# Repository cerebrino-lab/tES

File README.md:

# diy_tES
Eletro-estimulador transcraniano (tES)

## ATENÇÃO!
**Esse circuito pode causar danos graves e permanentes ou até a morte.
O projeto foi publicado apenas para fiz didátidos e não deve ser usado em seres humanos ou animais em hipótese alguma.
Estejam cientes!**

## Configuração dos parâmetros através de conexão serial.

Modos de operação:
-Modo corrente contínua (ainda não implementado): estímulo por corrente contínua ajustavel de 0mA á 2mA 
-Modo senoidal: onda senoidal simples, com frequência ajustavel de 1Hz á 255Hz e corrente de 0mA á 2mA pico a pico.
-Modo cruzado: onda senoidal modulada em amplitude na fase positiva por uma segunda onda. Frequências com ajuste independente de 1Hz á 255Hz e correntes de 0mA á 2mA pico a pico.
Parâmetros das ondas:

-Frequência: ajustável de 1 a 255 Hz.

-Amplitude: ajustável de 0.1 a 2,1mA.

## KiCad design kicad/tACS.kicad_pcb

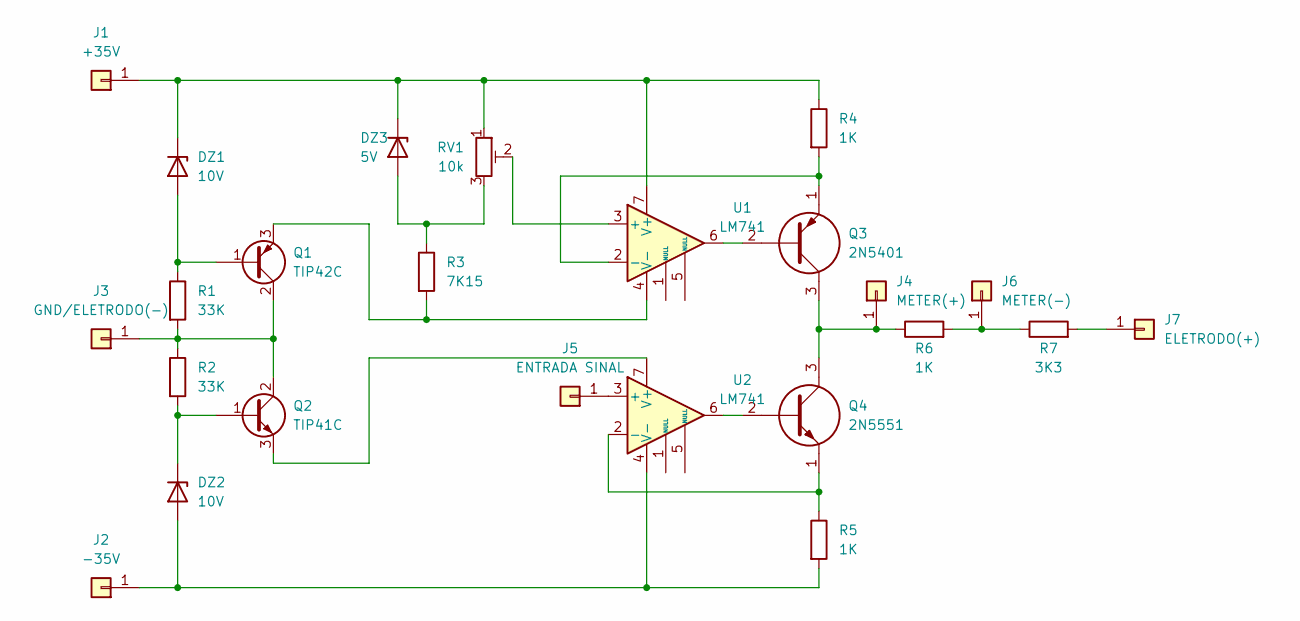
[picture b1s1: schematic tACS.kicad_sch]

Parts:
DZ1, DZ2: 10V; D_DO-41_SOD81_P7.62mm_Horizontal
DZ3: 5V; D_DO-41_SOD81_P7.62mm_Horizontal
J1: +35V; Pin_D0.7mm_L6.5mm_W1.8mm_FlatFork
J2: -35V; Pin_D0.7mm_L6.5mm_W1.8mm_FlatFork
J3: GND/ELETRODO(-); Pin_D0.7mm_L6.5mm_W1.8mm_FlatFork
J4: METER(+); Pin_D0.7mm_L6.5mm_W1.8mm_FlatFork
J5: ENTRADA SINAL; Pin_D0.7mm_L6.5mm_W1.8mm_FlatFork
J6: METER(-); Pin_D0.7mm_L6.5mm_W1.8mm_FlatFork
J7: ELETRODO(+); Pin_D0.7mm_L6.5mm_W1.8mm_FlatFork
Q1: TIP42C; TO-220-3_Vertical
Q2: TIP41C; TO-220-3_Vertical
Q3: 2N5401; TO-92; Manufacturer_Part_Number 2N5401
Q4: 2N5551; TO-92; Manufacturer_Part_Number 2N5551; Mouser Part Number 863-2N5551
R1, R2: 33K; R_Axial_DIN0204_L3.6mm_D1.6mm_P7.62mm_Horizontal
R3: 7K15; R_Axial_DIN0204_L3.6mm_D1.6mm_P7.62mm_Horizontal
R4, R6: 1K; R_Axial_DIN0204_L3.6mm_D1.6mm_P7.62mm_Horizontal
R5: 1K; R_Axial_DIN0204_L3.6mm_D1.6mm_P5.08mm_Vertical
R7: 3K3; R_Axial_DIN0204_L3.6mm_D1.6mm_P7.62mm_Horizontal
RV1: 10k; Potentiometer_Bourns_3296W_Vertical
U1, U2: LM741; DIP-8_W7.62mm_LongPads

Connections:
unnamed: DZ1.2 (A), Q1.1 (B), R1.1
unnamed: DZ1.1 (K), DZ3.1 (K), J1.1, R4.1, RV1.1, U1.7 (V+)
unnamed: DZ2.2 (A), J2.1, R5.2, U2.4 (V-)
unnamed: DZ2.1 (K), Q2.1 (B), R2.2
unnamed: DZ3.2 (A), R3.1, RV1.3
unnamed: J3.1, Q1.2 (C), Q2.2 (C), R1.2, R2.1
unnamed: J4.1, Q3.3, Q4.3, R6.1
unnamed: J5.1, U2.3 (+)
unnamed: J6.1, R6.2, R7.1
unnamed: J7.1, R7.2
unnamed: Q1.3 (E), R3.2, U1.4 (V-)
unnamed: Q2.3 (E), U2.7 (V+)
unnamed: Q3.2, U1.6
unnamed: Q4.2, U2.6
unnamed: RV1.2, U1.3 (+)
unnamed: Q3.1, R4.2, U1.2 (-)
unnamed: Q4.1, R5.1, U2.2 (-)

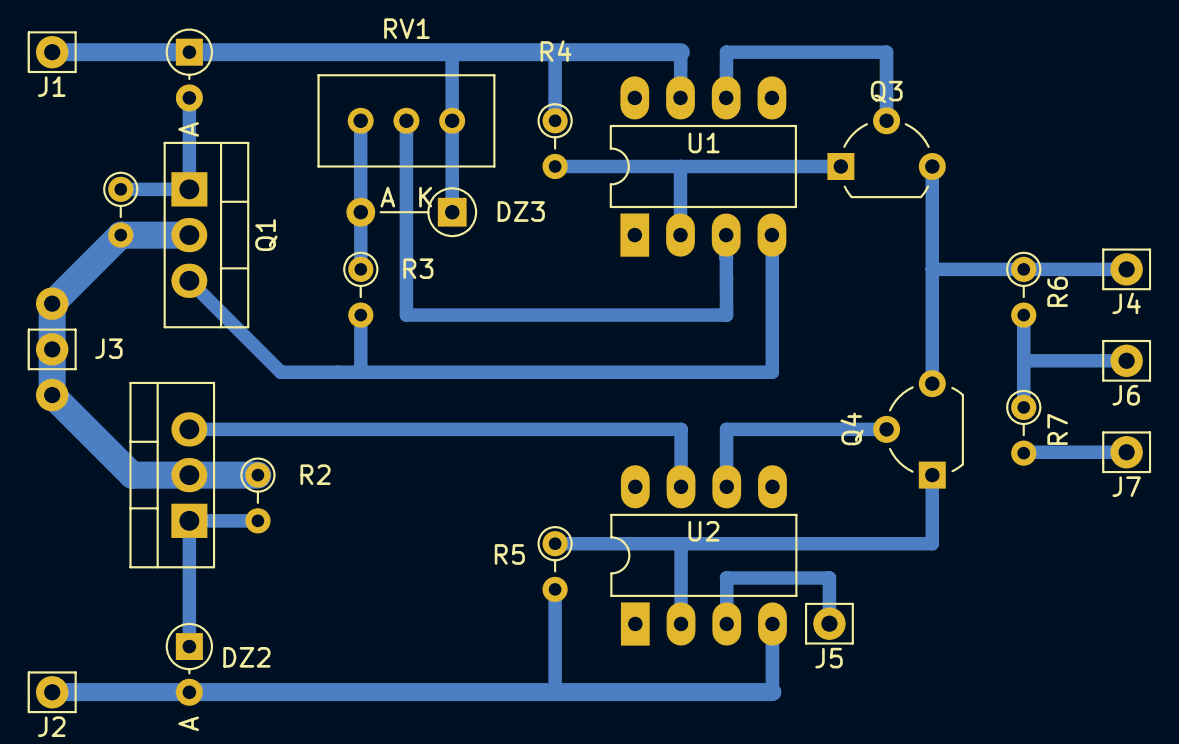
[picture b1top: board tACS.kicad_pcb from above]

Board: 2 copper layers, 24 parts (0 on the bottom side), 17 nets.

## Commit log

2023-12-10 Create teste
2024-02-22 Menu simplificado
2024-12-21 Create LICENSE
